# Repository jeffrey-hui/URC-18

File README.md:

# URC-18

Hello there! Welcome to the URC-18 github repository. Here is where all the URC code for 2018 is see teamr3/URC for 2017.
The file structure of this repo is fairly simple:

| File/Directory | Purpose |
| :------------- | ------: |
| rosws | contains all the packages we have written in ros, packages that are deps should either be done with wstool or rosdep |
| scripts | contains various scripts to make things easier |
| microcontroller | contains platformio projects for each microcontroller |
| pcbs | contains PCB eagle design files |

## getting setup

To get setup, do the following:

1. Clone this repository

...Make sure you put it somewhere memorable, you're going to be cd-ing to it a lot.

2. From the *root* of the repo, run `scripts/setup.sh`

...The script will ask you about some things, and might prompt you to install some stuff.
...Once it's done, it'll build everything. If this fails, it probably just means we have some bad code checked in.

3. That's it!

## requirements

- a working ROS install, currently we're using kinetic.

# branches

In order to ensure working code on the master branch, keep new features/packages on their own branches. If you are re-writing something, make a new branch for the rewrite, and
base new packages off of that branch. For example:

```
+-- master
    + -- science-excel
    + -- new-auto
         + -- move_base_config
    + -- ros_control
         + new_arm
         + new_drive
```

---
*Master should always be good working code*
---

When a feature/bugfix is done on a branch, it can be merged to its parent. For example, if `new_arm` in the example was done, it would get merged to `ros_control`. When all of `ros_control` is done, it
gets merged to master. Try and use pull requests for bigger merges, especially when re-writing large portions of existing code.

# documentation

The decision has been made to use readthedocs, the url is r3-urc18.readthedocs.io.
Documentation is in the docs/ folder. Information on how to document is coming soon

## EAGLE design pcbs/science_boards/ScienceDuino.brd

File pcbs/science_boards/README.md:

# TODO
- [ ] Add optocouplers for all digital sensors, refer to main board for optocoupler
and the required passives (attempt to find the surface mount version of the
optocoupler used on the main board)
- [ ] Add 7V supply for annemometor
- [ ] decoupling capacitors for all supply lines
- [ ] bidirectional logic level converter for i2c, refer to battery boards
for how to do this (Ask Gabe if you cant figure it out)

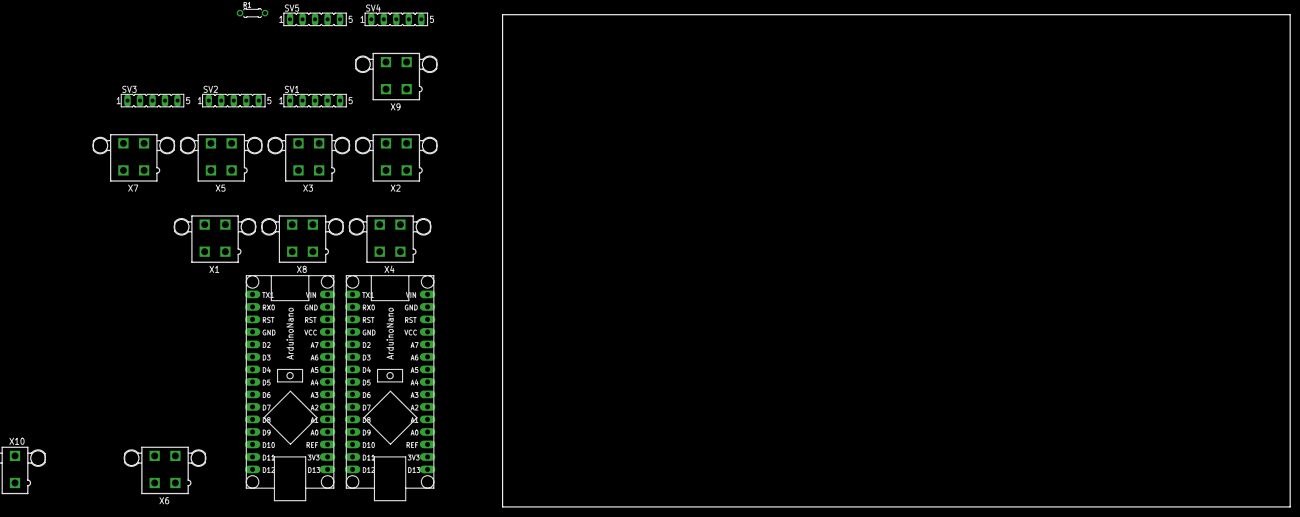
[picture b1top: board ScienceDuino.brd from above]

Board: 2 copper layers, 160.0 x 100.0 mm, 18 parts (0 on the bottom side), 23 nets, no tracks yet.

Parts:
A1, A2: ARDUINONANO
R1: 10K; 0204/5
SV1, SV2, SV3, SV4, SV5: FE05-1
X1: Barometer; 5566-4
X2: Anemometer; 5566-4
X3: EC; 5566-4
X4: EC-Temperature; 5566-4
X5: PH; 5566-4
X6: Temperature+Humidity; 5566-4
X7: Hydrogen; 5566-4
X8: Geiger counter; 5566-4
X9: Dust sensor; 5566-4
X10: 5566-2

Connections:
3V3: A1.17, A2.17
CLK_TH: A1.7, X6.2
DATA1_ANO: A1.20, X2.1
DATA1_DUST: A1.25, X9.1
DATA1_EC: A1.21, X3.1
DATA1_ECT: A1.8, X4.1
DATA1_GEI: A1.5, X8.1
DATA1_HY: A1.19, X7.1
DATA1_PH: A1.22, X5.1
DATA1_TH: A1.6, R1.2, X6.1
DATA2_DUST: A1.9, X9.2
DO_RX: A2.5, SV4.5
DO_RX1: SV1.5, SV3.5
DO_TX: A2.6, SV4.4
DO_TX1: SV1.4, SV3.4
GND: A1.4, A1.29, A2.4, A2.29, SV1.3, SV3.3, SV4.3, X1.4, X2.4, X3.4, X4.4, X5.4, X6.4, X7.4, X8.4, X9.4, X10.2
PGND: SV2.5, SV5.5
PRB: SV2.4, SV5.4
REF: A1.18, A2.18
SCL: A1.24, X1.1
SDA: A1.23, X1.2
VCC: A1.27, A2.27, R1.1, SV2.3, SV3.1, SV4.1, SV5.3, X1.3, X3.3, X4.3, X5.3, X6.3, X7.3, X8.3, X9.3
VIN: A1.30, A2.30, X10.1

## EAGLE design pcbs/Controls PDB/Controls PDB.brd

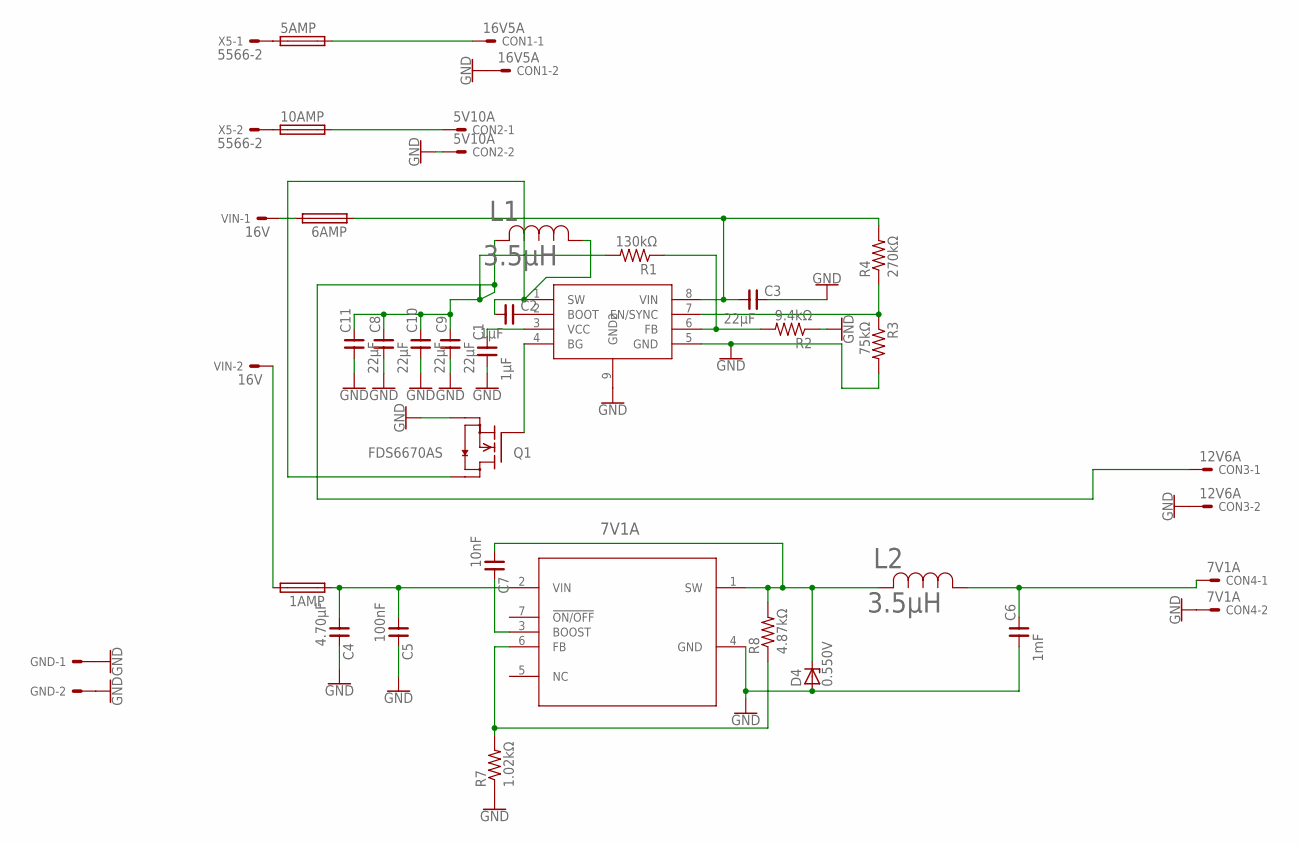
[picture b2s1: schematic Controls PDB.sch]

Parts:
1AMP, 5AMP, 6AMP, 10AMP: FUSEBLANK_5X20MM; FUSE_HOLDER_5X20MM
7V1A: LM2678T-3.3/NOPB; TA07B
C1, C2: 1µF; 1206
C3, C8, C9, C10, C11: 22µF; 1206
C4: 4.70µF; 1206
C5: 100nF; 1206
C6: 1mF; 1206
C7: 10nF; 1206
CON1: 16V5A; 5566-2
CON2: 5V10A; 5566-2
CON3: 12V6A; 5566-2
CON4: 7V1A; 5566-2
D4: 0.550V; SOD123F
GND: 5566-2
L1, L2: 3.5µH; IND_BOURNS_SRR1260
Q1: FDS6670AS; SO-8
R1: 130kΩ; R1206
R2: 9.4kΩ; R1206
R3: 75kΩ; R1206
R4: 270kΩ; R1206
R7: 1.02kΩ; R1206
R8: 4.87kΩ; R1206
U$1: SOIC; SOIC127P599X175-9N
VIN: 16V; 5566-2
X5: 5566-2

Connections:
GND: 7V1A.4 (GND), C1.P$1 (1), C3.P$2 (2), C4.P$2 (2), C5.P$2 (2), C6.P$1 (1), C8.P$1 (1), C9.P$1 (1), C10.P$1 (1), C11.P$1 (1), CON1.2, CON2.2, CON3.2, CON4.2, D4.A, GND.1, GND.2, Q1.3 (S), R2.1, R3.2, R7.1, U$1.5 (GND), U$1.9 (GND2)
unnamed: C2.P$2 (2), U$1.2 (BOOT)
unnamed: C1.P$2 (2), U$1.3 (VCC)
unnamed: R1.1, R2.2, U$1.6 (FB)
unnamed: 10AMP.2, CON2.1
unnamed: 5AMP.2, CON1.1
unnamed: 5AMP.1, X5.1
unnamed: 10AMP.1, X5.2
unnamed: 1AMP.2, VIN.2
unnamed: 6AMP.1, C3.P$1 (1), R4.2, U$1.8 (VIN)
unnamed: R3.1, R4.1, U$1.7 (EN/SYNC)
unnamed: C6.P$2 (2), CON4.1, L2.1
unnamed: 6AMP.2, VIN.1
unnamed: Q1.4 (G), U$1.4 (BG)
unnamed: 7V1A.1 (SW), C7.P$1 (1), D4.C, L2.2, R8.2
unnamed: 1AMP.1, 7V1A.2 (VIN), C4.P$1 (1), C5.P$1 (1)
unnamed: 7V1A.6 (FB), R7.2, R8.1
unnamed: 7V1A.3 (BOOST), C7.P$2 (2)
unnamed: C2.P$1 (1), L1.1, Q1.8 (D), U$1.1 (SW)
unnamed: C8.P$2 (2), C9.P$2 (2), C10.P$2 (2), C11.P$2 (2), CON3.1, L1.2, R1.2

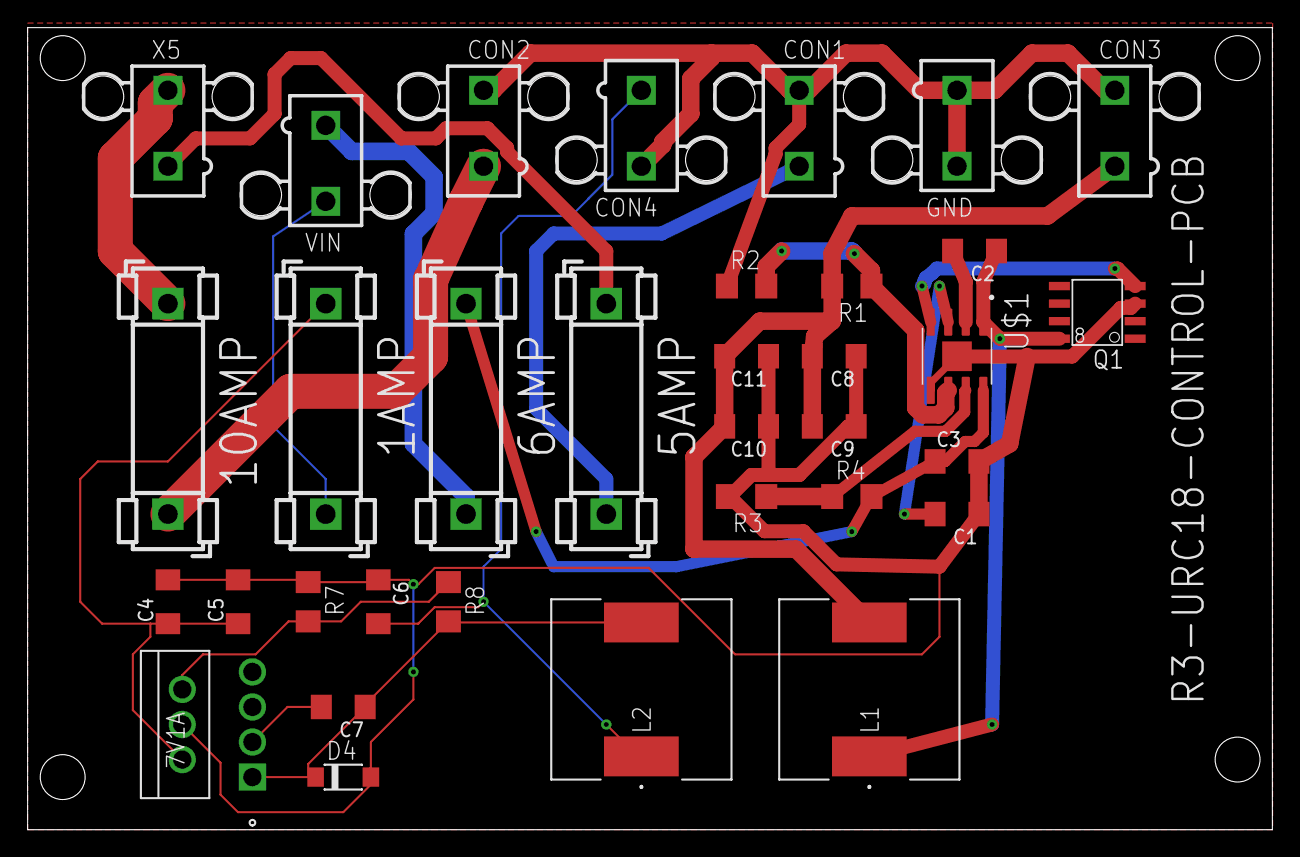
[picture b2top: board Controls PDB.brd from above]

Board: 2 copper layers, 90.2 x 58.1 mm, 34 parts (0 on the bottom side), 20 nets.

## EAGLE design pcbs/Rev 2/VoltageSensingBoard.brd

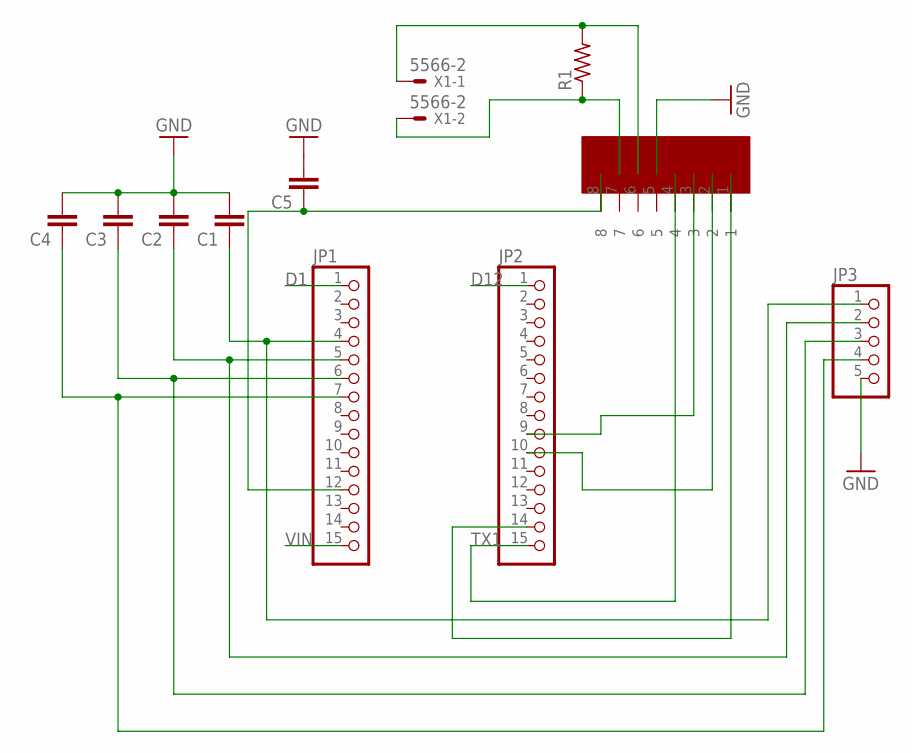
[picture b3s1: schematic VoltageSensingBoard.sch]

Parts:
C1, C2, C3, C4, C5: C5/2.5; C5B2.5
JP1, JP2: PINHD-1X15; 1X15
JP3: PINHD-1X5; 1X05
R1: R-US_0204/7; 0204/7
U$1: THVD1550; SO08
X1: 5566-2

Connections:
D1: JP1.1
D12: JP2.1
GND: C1.2, C2.2, C3.2, C4.2, C5.2, JP3.5, U$1.5
unnamed: C1.1, JP1.4, JP3.1
unnamed: C3.1, JP1.6, JP3.3
unnamed: C4.1, JP1.7, JP3.4
unnamed: R1.2, U$1.6, X1.1
unnamed: R1.1, U$1.7, X1.2
unnamed: C2.1, JP1.5, JP3.2
unnamed: C5.1, JP1.12, U$1.8
unnamed: JP2.10, U$1.2
unnamed: JP2.14, U$1.1
unnamed: JP2.9, U$1.3
TX1: JP2.15, U$1.4
VIN: JP1.15

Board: 2 copper layers, 11 parts (0 on the bottom side), 12 nets, no tracks yet.

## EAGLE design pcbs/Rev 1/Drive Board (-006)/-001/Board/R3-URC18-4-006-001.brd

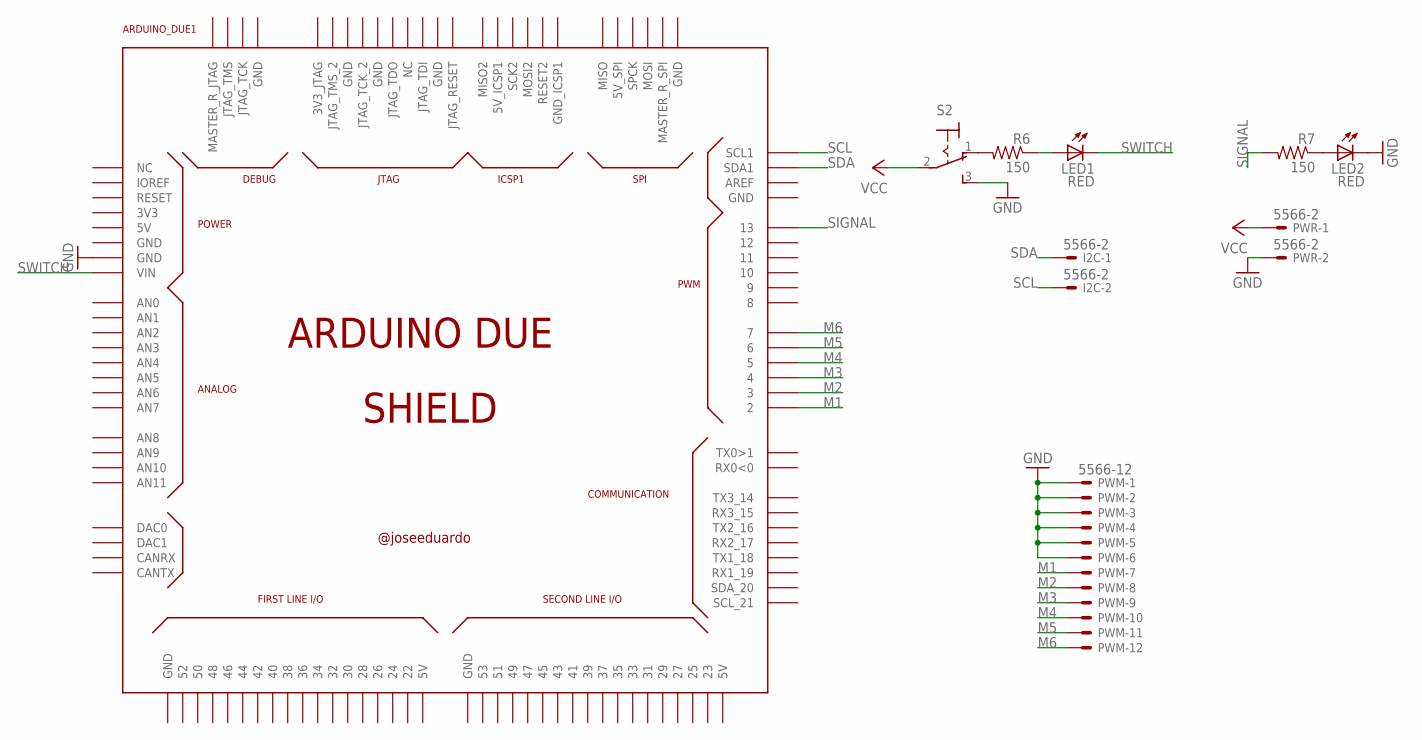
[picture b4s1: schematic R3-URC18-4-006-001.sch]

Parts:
ARDUINO_DUE1: ARDUINO_DUE_SHIELD
I2C: 5566-2
LED1, LED2: RED; LED5MM
PWM: 5566-12
PWR: 5566-2
R6, R7: 150; 0207/10
S2: M9040P

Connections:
GND: ARDUINO_DUE1.GND_1 (GND), LED2.K (C), PWM.1, PWM.2, PWM.3, PWM.4, PWM.5, PWM.6, PWR.2, S2.3 (S)
M1: ARDUINO_DUE1.2, PWM.7
M2: ARDUINO_DUE1.3, PWM.8
M3: ARDUINO_DUE1.4, PWM.9
M4: ARDUINO_DUE1.5, PWM.10
M5: ARDUINO_DUE1.6, PWM.11
M6: ARDUINO_DUE1.7, PWM.12
unnamed: R6.2, S2.1 (O)
unnamed: LED1.A, R6.1
unnamed: LED2.A, R7.1
SCL: ARDUINO_DUE1.SCL1, I2C.2
SDA: ARDUINO_DUE1.SDA1, I2C.1
SIGNAL: ARDUINO_DUE1.13, R7.2
SWITCH: ARDUINO_DUE1.VIN, LED1.K (C)
VCC: PWR.1, S2.2

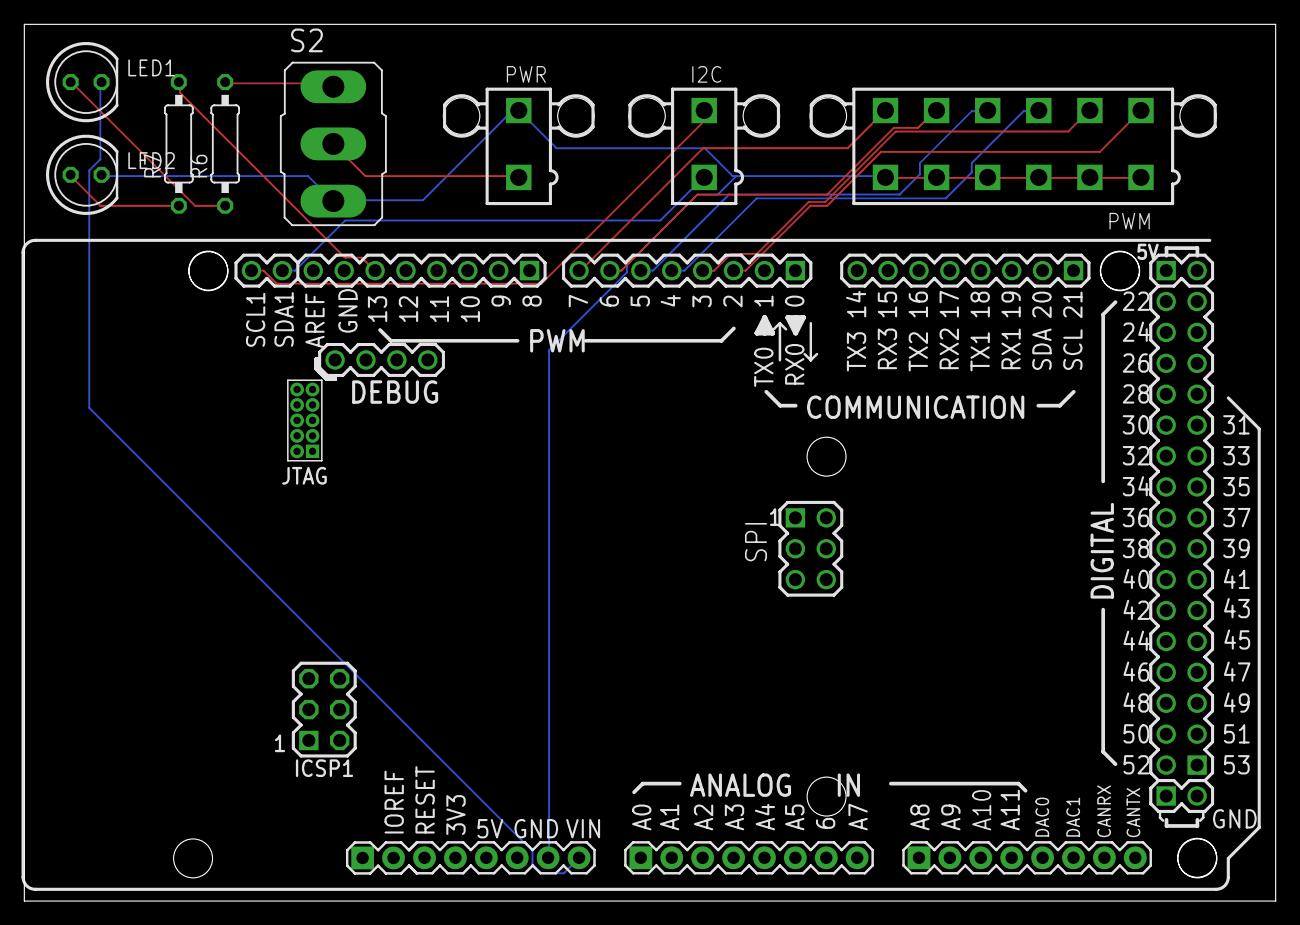
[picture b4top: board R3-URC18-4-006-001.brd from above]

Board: 2 copper layers, 102.8 x 72.1 mm, 9 parts (0 on the bottom side), 15 nets.

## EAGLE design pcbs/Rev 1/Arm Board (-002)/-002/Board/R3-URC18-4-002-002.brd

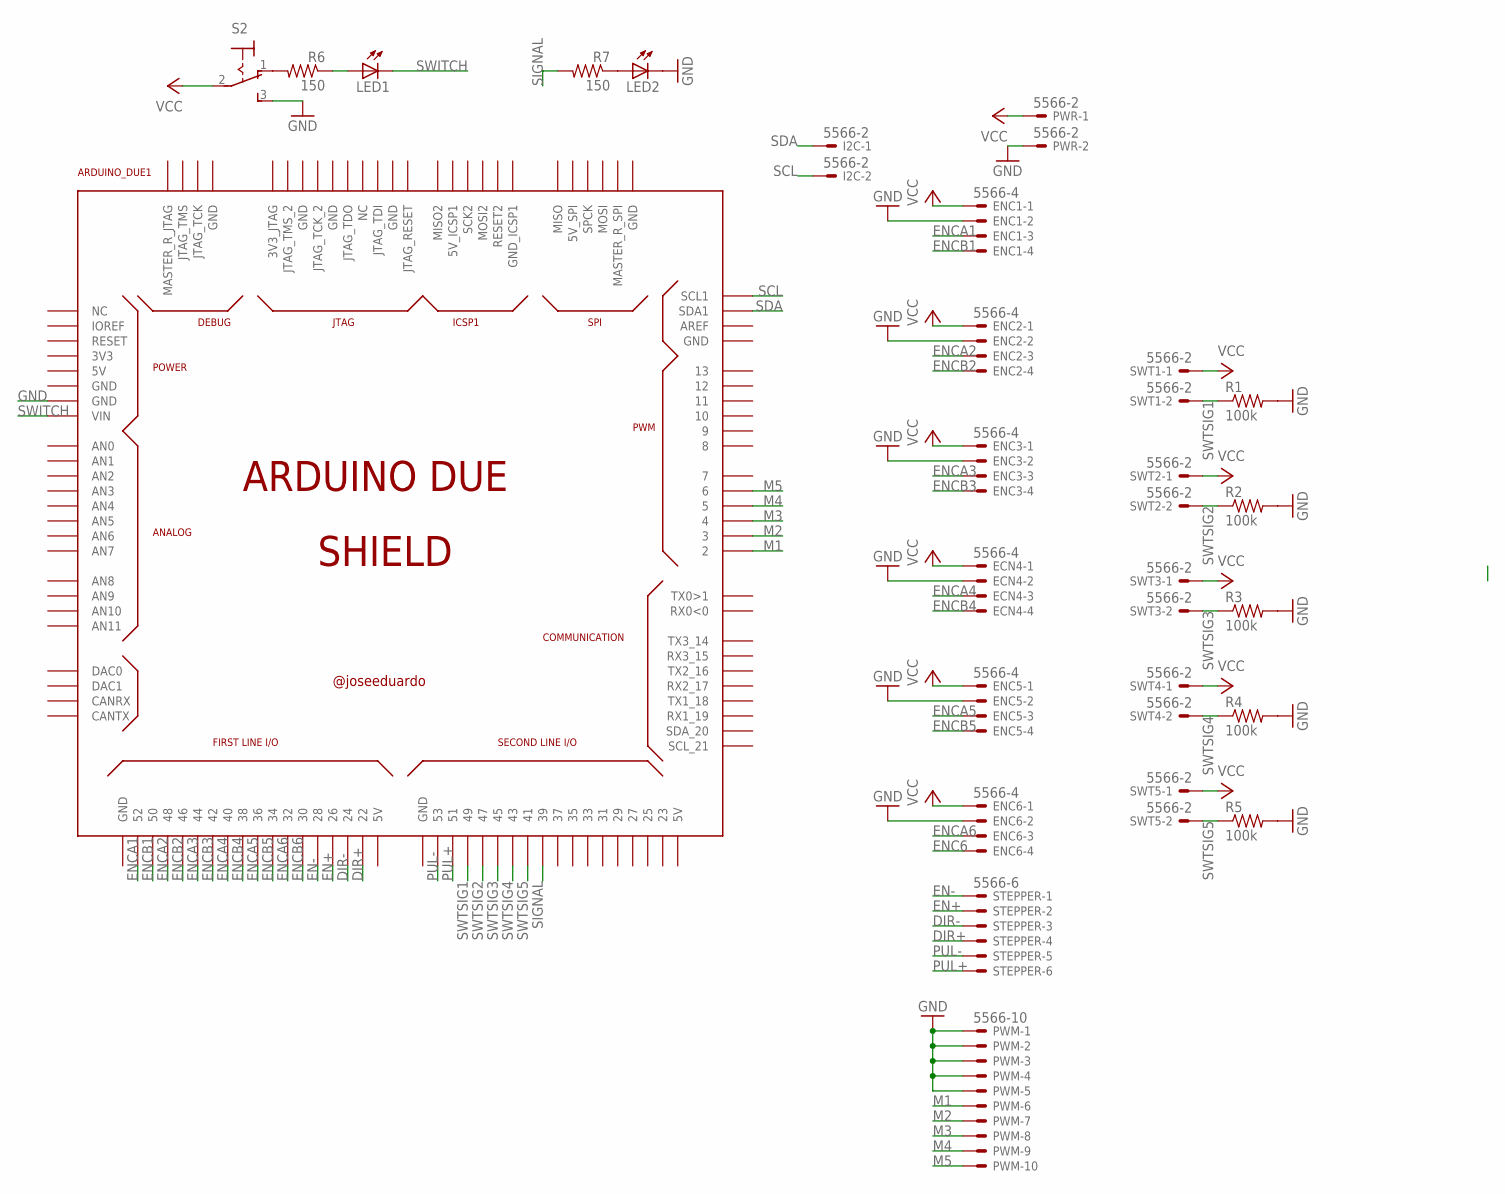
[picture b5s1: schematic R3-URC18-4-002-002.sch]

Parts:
ARDUINO_DUE1: ARDUINO_DUE_SHIELD
ECN4: 5566-4
ENC1, ENC2, ENC3, ENC5, ENC6: 5566-4
I2C: 5566-2
LED1, LED2: LED5MM
PWM: 5566-10
PWR: 5566-2
R1, R2, R3, R4, R5: 100k; 0207/10
R6, R7: 150; 0207/10
S2: M9040P
STEPPER: 5566-6
SWT1, SWT2, SWT3, SWT4, SWT5: 5566-2

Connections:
DIR+: ARDUINO_DUE1.22, STEPPER.4
DIR-: ARDUINO_DUE1.24, STEPPER.3
EN+: ARDUINO_DUE1.26, STEPPER.2
EN-: ARDUINO_DUE1.28, STEPPER.1
ENC6: ENC6.4
ENCA1: ARDUINO_DUE1.52, ENC1.3
ENCA2: ARDUINO_DUE1.48, ENC2.3
ENCA3: ARDUINO_DUE1.44, ENC3.3
ENCA4: ARDUINO_DUE1.40, ECN4.3
ENCA5: ARDUINO_DUE1.36, ENC5.3
ENCA6: ARDUINO_DUE1.32, ENC6.3
ENCB1: ARDUINO_DUE1.50, ENC1.4
ENCB2: ARDUINO_DUE1.46, ENC2.4
ENCB3: ARDUINO_DUE1.42, ENC3.4
ENCB4: ARDUINO_DUE1.38, ECN4.4
ENCB5: ARDUINO_DUE1.34, ENC5.4
ENCB6: ARDUINO_DUE1.30
GND: ARDUINO_DUE1.GND_1 (GND), ECN4.2, ENC1.2, ENC2.2, ENC3.2, ENC5.2, ENC6.2, LED2.K (C), PWM.1, PWM.2, PWM.3, PWM.4, PWM.5, PWR.2, R1.2, R2.2, R3.2, R4.2, R5.2, S2.3 (S)
M1: ARDUINO_DUE1.2, PWM.6
M2: ARDUINO_DUE1.3, PWM.7
M3: ARDUINO_DUE1.4, PWM.8
M4: ARDUINO_DUE1.5, PWM.9
M5: ARDUINO_DUE1.6, PWM.10
unnamed: R6.2, S2.1 (O)
unnamed: LED1.A, R6.1
unnamed: LED2.A, R7.1
PUL+: ARDUINO_DUE1.51, STEPPER.6
PUL-: ARDUINO_DUE1.53, STEPPER.5
SCL: ARDUINO_DUE1.SCL1, I2C.2
SDA: ARDUINO_DUE1.SDA1, I2C.1
SIGNAL: ARDUINO_DUE1.39, R7.2
SWITCH: ARDUINO_DUE1.VIN, LED1.K (C)
SWTSIG1: ARDUINO_DUE1.49, R1.1, SWT1.2
SWTSIG2: ARDUINO_DUE1.47, R2.1, SWT2.2
SWTSIG3: ARDUINO_DUE1.45, R3.1, SWT3.2
SWTSIG4: ARDUINO_DUE1.43, R4.1, SWT4.2
SWTSIG5: ARDUINO_DUE1.41, R5.1, SWT5.2
VCC: ECN4.1, ENC1.1, ENC2.1, ENC3.1, ENC5.1, ENC6.1, PWR.1, S2.2, SWT1.1, SWT2.1, SWT3.1, SWT4.1, SWT5.1

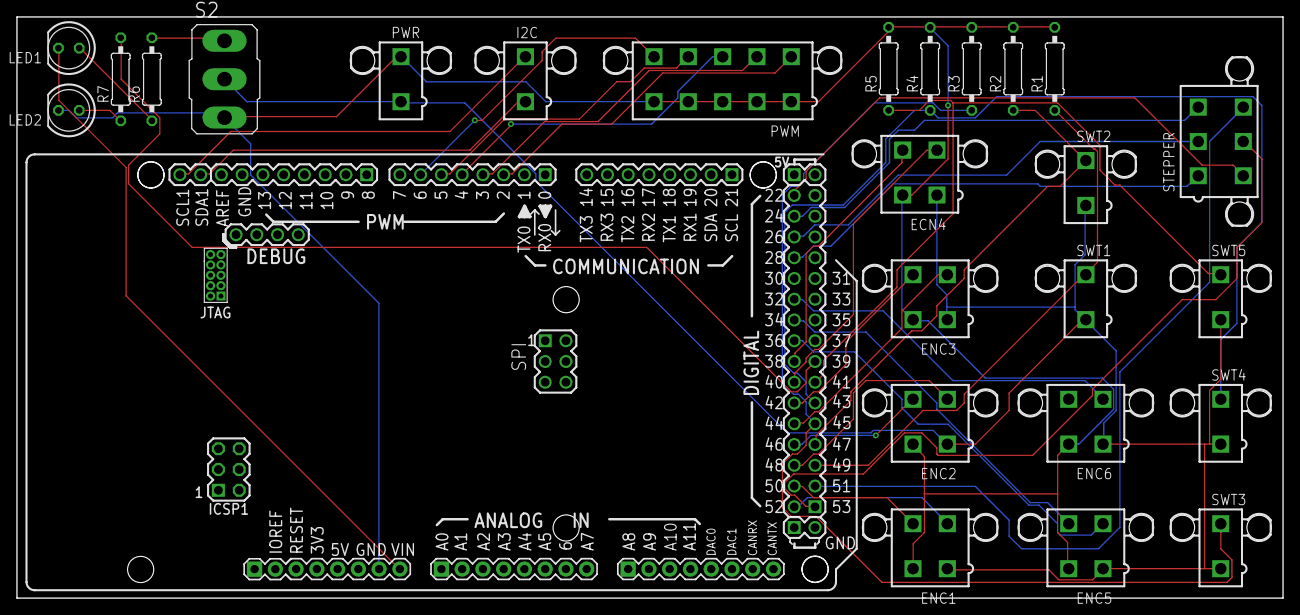
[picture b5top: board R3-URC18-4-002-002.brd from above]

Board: 2 copper layers, 154.9 x 71.1 mm, 26 parts (0 on the bottom side), 36 nets.

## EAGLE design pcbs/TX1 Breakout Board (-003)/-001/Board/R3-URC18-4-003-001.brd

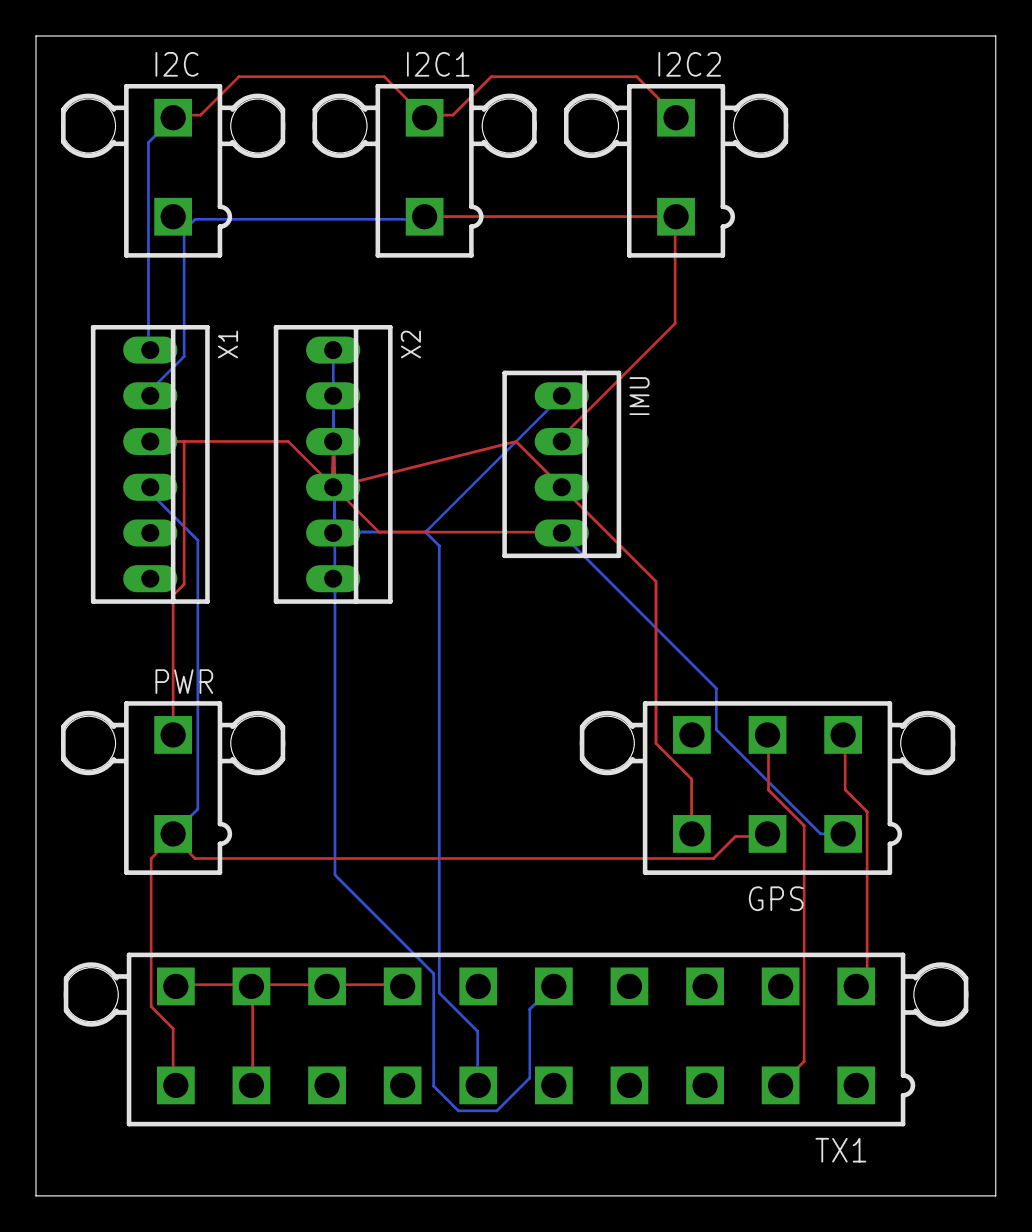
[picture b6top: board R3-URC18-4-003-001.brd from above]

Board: 2 copper layers, 53.3 x 64.4 mm, 9 parts (0 on the bottom side), 10 nets.

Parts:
GPS: 5566-6
I2C, I2C1, I2C2: 5566-2
IMU: 22-23-2041
PWR: 5566-2
TX1: 5566-20
X1, X2: 22-23-2061

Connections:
GND: GPS.1, IMU.4, PWR.2, X1.3, X2.3
SCL: I2C.2, I2C1.2, I2C2.2, X1.1
SCL_LV: IMU.1, TX1.6, X2.2
SDA: I2C.1, I2C1.1, I2C2.1, IMU.2, X1.2
SDA_LV: TX1.15, X2.1
UART_RX0: GPS.4, TX1.11
UART_TX0: GPS.5, TX1.2
VCC: GPS.2, PWR.1, TX1.10, X1.4
VDD: GPS.3, IMU.3, X2.4
_GND: TX1.9, TX1.17, TX1.18, TX1.19, TX1.20

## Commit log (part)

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2017-08-03 initial structure
2017-08-03 put microcontroller in git for now
2017-08-04 New stuff with urdf
    Also did some work on the setup script, thought i'd push it up
2017-08-04 working gazebo config w/ simple rover
2017-08-06 holy code dump. also moveit works now and there's an arm
2017-08-07 add documentation, might of also added the zed (might)
2017-08-07 fix doc code blocks
2017-08-09 demo
2017-08-16 Fix stupid sudo bug
2017-08-22 add base encoder project
2017-09-07 move moveit away
2017-09-07 get moveit in seperate branch
2017-09-07 fix .gitignore for less accidental commits
    add wstool packages to .gitignore on master and rebase
2017-09-12 hkjajasdflhasdfhjlasdfkjgh
    (changed the README)
    whatever you want
2017-09-26 new brnch
    new gazebo stuff
2017-09-26 TRAC-IK (#3)
    * start tracik
    (yes i know i took forever i was busy ok?)
    * basic header stuffs
    need to do a bit more reading
    use zsh!
    * go fish
2017-09-28 slightly nicer texturing & better sizing
2017-09-28 mergey
2017-09-28 All pcbs (#5)
    * Added Encoder Stuffs
    * fixed stuff that mini matt made apparent to me
    * v1.0
    * armboard Rev 2
    * drive board v1
    * tx1 board completed
2017-10-01 Create .gitattributes
    Fixes stupid git linguist
2017-10-04 new ARM!!!!!
2017-10-04 better naming
2017-10-05 Gazebo outdoor world (#6)
    * new brnch
    new gazebo stuff
    * new brnch
    new gazebo stuff
    * slightly nicer texturing & better sizing
2017-10-27 servo test
2017-10-27 sync
2017-10-27 ros_control drive
    controllers are working, testing of hardware is probably happening on saturday
2017-10-27 what
2017-10-27 docs v. 1
2017-10-27 test2
2017-10-27 AMAZING DOCUMENTATION
2017-10-27 FOR TESTIJNG
2017-10-27 test codez
2017-10-27 moar docs
2017-10-27 sumting
2017-10-27 temp
2017-10-27 fix idiotic negation
2017-10-27 something
2017-10-31 Simple drive+ros control (#4)
    * create simple drive
    * simple drive teleop + launch
    * fix launch file + new launch file
    should be done with simple drive now (i hope).
    currently tuned to ramsbot configuration!
    * compiles correctly (clion y u miss errors?)
2017-11-01 unnessecary codeos
2017-11-06 segment pt1
2017-11-06 Fix rover_control.launch
    (cherry picked from commit a8eec79)
2017-11-06 Fix rover_control.launch, pt. 2
    (cherry picked from commit f9967ce)
2017-11-07 Remove bogus directory
2017-11-09 start work
2017-11-09 fix constants
2017-11-22 linearize
2017-11-22 Remove simple_drive.launch
    It was just a poop anyways
2017-11-23 Fix gabes stupid commit error
2017-11-23 add more stuff to make auton easier
2017-11-23 merge in new teleop
    (cherry picked from commit ab3c0ac)
2017-11-28 something yay it kind of works but stupid stuff makes it doesn't
2018-01-12 create stereo camera
2018-01-12 Wheel friction fix (#9)
    * Remove simple_drive.launch
    It was just a poop anyways
    * yippe yooooooo!
    in other words, it functions now
2018-01-18 Randomized blabla
2018-01-18 yippe yooooooo!
    in other words, it functions now
    (cherry picked from commit a7708cd)
2018-01-19 pretty much functioning!
2018-01-23 add nav docs
2018-01-25 more odometry locations, added a laser to the urdf (probably will be unused)
    added parameters to the max wheel speed to prepare for fixing proper values for real rover
    these values need fixing for actual rover operations
2018-01-26 Rover cameras (#10)
    * Remove simple_drive.launch
    It was just a poop anyways
    * intial commit to usb_camea
    * dofus
    * add rotater
    * dofus
2018-01-26 fix authors in docs
2018-01-26 move eml_uberdriver
2018-01-27 almost done docs for eml_uberdriver
    WARNING: this will probably get moved out to rtd for a seperate system, but for now
    it is staying here
2018-02-02 fix uberfirmware
2018-02-08 changed science scripts to pio
2018-02-08 fix mac's stupid filesystem poop
2018-02-09 sensors documentation summary
2018-02-09 unkill science
2018-02-09 R3_IDON_O_TLIK_ENAMING_BRANCHES_LIKE_THIS_AAAA (#11)
    * Organizing
    * Does not work yet
    * Add pcbs to README
    * Create science_boards
    * Delete science_boards
    * Create read_me
2018-02-09 Emergency mac removal
2018-02-15 calibrate stereo
2018-02-16 begin work on rover arm,
2018-02-16 more arm
2018-02-16 change urdf to have similar names to stereo cam
2018-02-16 add disp_to_depth
2018-02-16 make it work with stereo & simulation (hopefully)
2018-02-17 stuff in progress
2018-02-20 current version
2018-02-21 reformat arm to a better format
2018-02-21 add science gripper
2018-02-21 reorg arm_hw
2018-02-22 begin science arm
2018-02-22 tune pids better
2018-02-23 begin as
2018-02-26 asdf - asdf
2018-03-02 added logic level converter
2018-03-02 Ground fill
2018-03-02 init commit
2018-03-02 Ground fill for realz
2018-03-02 add various things
2018-03-03 change outdoor_world to support multiple grippers
    a sane commit message?
2018-03-03 SUPER BETA BRANCH
    sure i merged it, not well
2018-03-03 Stuff
2018-03-04 begin moveit config for rover_science_arm
    ya
2018-03-05 begin adding launch files for moveit
2018-03-06 finish main confgi
2018-03-06 started adding moveit to controller
2018-03-07 AAAAAH (it works)
2018-03-13 init secondary auto (please work)
2018-03-14 new cam config
2018-03-14 actually function
2018-03-14 editted the read me
2018-03-14 make it look really nice
2018-03-15 really should be a working tennis ball rayfinder
    todo:
    - write stereo
    - write intersector/correlator
2018-03-15 remove old
2018-03-16 add tennis ball predictor
2018-03-17 start work on new stereo config
2018-03-17 finish new stereo config (needs testing)
2018-03-18 switch sim back over to stereo...
2018-03-19 asdsada
2018-03-19 fuck hamza
2018-03-22 I hate hamza 2
2018-03-22 Fuck Mk
2018-04-03 fix urdf for stereo cameras
2018-04-03 Stereo urdf (#12)
    * servo test
    * change back to victors!
    t
    * servo test
    * change back to victors!
    t
2018-04-03 51 dollars for a new calibration...
    MONEY WELL SPENT!!!!
    (cherry picked from commit a9eb967)
2018-04-03 holy fuck
2018-04-05 add heading, start drive
2018-04-06 Final commit for battery pcb, added resistor values #2
2018-04-07 make rover_nav config only use stereo
    also use cloud_obstacles
2018-04-07 some odom config
2018-04-07 add obstacle segement, undo some of last commit
2018-04-07 YES
    NO
    MAYBE
    PERHAPS
    What are commit messsages?
2018-04-08 add horizon
2018-04-09 Control pcb
2018-04-09 Final final changes
2018-04-10 Uberfirmware split (#13)
    * move eml_uberdriver
    * almost done docs for eml_uberdriver
    WARNING: this will probably get moved out to rtd for a seperate system, but for now
    it is staying here
    * fix uberfirmware
    * update docs for arduino protocol to be pointing to eml_uberdriver
2018-04-11 add toggle button
2018-04-11 yaaaay
2018-04-12 wrong bloody frame id
2018-04-12 looks really nice (also updated to use newer)
2018-04-14 add stereo tennis ball tracking, and clean up and add logging
2018-04-14 add launch file
2018-04-14 add to main launch file
2018-04-14 improve confidence function
2018-04-14 add comments?
2018-05-02 set rtabmap to make a BLOODY MASSIVE MAP
    yay
2018-05-02 start the thiing that adds lines to the costmap that guides the rover to do things
2018-05-03 internal documentation
    AaaAaaAaaaaaAAAAAaaaAAAAA
    - "it does the thing that does the stuff"
    - yippee
    yay
2018-05-04 Set constants for drive (we really need a develop branch)
    next year, maybe
2018-05-04 Upside Down Smiley Face
    dab
2018-05-06 Pre-actionlib and tf (working)
2018-05-07 work in progress...
2018-05-08 asdf rover develop
2018-05-09 further change
2018-05-09 start work on new arm software
    for test
    it'll work
    i promise
    no i dont
    neveer mind
2018-05-10 maybe working code for arm
2018-05-10 changed the address to match hardware
2018-05-11 stop spamming a you git
2018-05-11 compilable skeleton of how i imagine auton
    publishes "dummy" text for now. Need to understand GPS coordinates and need matthiew to tell me topics publishing and where to publish my data to.
    Will add PID soon.
2018-05-11 yayyayayayaya
    why am i so tired
2018-05-11 working P controller, publishes to desired topic. still need GPS thingy
2018-05-11 clean up
2018-05-12 add motor constants
2018-05-12 2 is not wired?
2018-05-13 lines_layer now works
    now for orchestration, so you don't need twenty billion terminals to run it all
2018-05-13 start work on nav_executive
    also known as "THE ORCHESTRATOR" to those who listen to my ramblings
    and don't know what i'm talking about
2018-05-13 nav_executive that seems to work
2018-05-14 YASSSS
2018-05-14 HUZZAH (it works)
    this is a matthew commit, under gabe's account(maybe)
2018-05-15 implemented control_toolbox: dankness +1
2018-05-15 last minute changes
2018-05-15 Arm software (#14)
    SQUAAAAASH it and merge it
    woopeee
    * Start new arm
    including new stars like:
    - the poles
    - the box
2018-05-15 added GPS and Mag input
2018-05-16 start imugps
2018-05-16 add les units
2018-05-16 update imu posistion
2018-05-16 remove the large amount of errors
2018-05-17 fuckit
2018-05-17 for crying out loud please don't pollute the git repo
2018-05-17 angle is now from mag instead of gps
2018-05-17 added speed limit so rover wont kill someone as minimat suggested
2018-05-19 fine
2018-05-19 better math
2018-05-19 added mag and gps subscribe
2018-05-20 Woopeee GPS
2018-05-20 fuckit 2: electric boogaloo
2018-05-20 new auton w/o move_base
2018-05-20 new auton that works
2018-05-20 add gps
2018-05-20 tf node?
2018-05-20 stupid
2018-05-20 remove nulls
2018-05-20 add gripper
2018-05-20 remove
2018-05-20 dd more debugs
2018-05-20 woopee
2018-05-23 also fixed the set robot as master script
2018-05-23 stuff??
2018-05-23 trash code
2018-05-23 fixing hamzas cancer
2018-05-23 not so shit anymore
2018-05-23 please stop annoying me
2018-05-24 Arm software (#16)
    * Start new arm
    including new stars like:
    - the poles
    - the box
    - the encap
    and returning players like:
2018-05-24 Arm software 2 (#17)
    * Start new arm
    including new stars like:
    - the poles
    - the box
    - the encap
    and returning players like:
2018-05-24 failde attempt at a launch file
2018-05-24 doesnt hog ram anymore
2018-05-24 aaaaa
2018-05-24 open source gps thingy
2018-05-24 add proxy node
2018-05-24 new mapviz
2018-05-25 add controller
2018-05-25 add camera controller code
2018-05-25 add cli
2018-05-25 add swapper code (TODO: add default cameras)
2018-05-27 added lib deps to science
2018-05-27 idk ??
2018-05-27 wth?
2018-05-27 add scriptypoos
2018-05-28 Updated nano code that should let it act as a slave to the tx1. It will send 20 bytes of data (first 2 bytes are a conversion factor, every 2 subsequent bytes are data from each of the 9 sensors atta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
2018-05-29 Revert "add"
    This reverts commit 27344e0e4d3e19c111b090619609b804c82ccae7.
2018-05-30 more work on jsmap
2018-05-30 Add swapper defaults and fix color (closes #17)
2018-05-30 added i2c to skience, skience needs to add the h2 sensors output to completed the payload
2018-05-30 emergitfixitnownownoyay
2018-05-30 thankyou git bisect
2018-05-30 jsmap now supports showing robot position & heading
2018-05-31 add jsmap
2018-05-31 gitgitigtitigiti
2018-05-31 fix build
2018-05-31 add points
2018-05-31 fixing the fuck number 2
2018-05-31 i2c stuff
2018-05-31 added i2c servo control
2018-05-31 fjeff
2018-05-31 add scieread node
2018-05-31 add csv saver
2018-05-31 doteleop
2018-05-31 Imus (#19)
    * servo test
    * change back to victors!
    t
    * servo test
    * change back to victors!
    t
2018-05-31 Update master launch file
    We need imu + gps for tommorow
2018-05-31 Fix cameras
2018-05-31 i got carried away
2018-05-31 diagnostics for cameras
2018-06-01 Improve Camera Switcher (#21)
    * i got carried away
    * diagnostics for cameras
    * fixyboi
2018-06-01 better teleop
2018-06-01 should be fixed
2018-06-01 new guis
2018-06-01 symbols
2018-06-01 fix mappybio
2018-06-02 ummmm
2018-06-02 dank dank dank
2018-06-02 5 seconds
2018-07-17 Watchdog (#18)
2018-07-18 Docs pt.1
2018-07-18 docs pt2
2018-07-18 docs pt3

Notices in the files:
parts and their libraries:
SparkFun-PowerSymbols: Licensing: Creative Commons ShareAlike 4.0 International - https://creativecommons.org/licenses/by-sa/4.0
